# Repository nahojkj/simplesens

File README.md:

# simplesens
simplesne is a simple Arduino-based environment sensing project.

MIT Licensed

The project consists of: 
  1. KiCAD schematic and layout
  2. GERBER production files for PCB
  3. Arduino code and binaries

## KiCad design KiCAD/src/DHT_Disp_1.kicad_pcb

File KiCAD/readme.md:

These are the design files for KiCAD

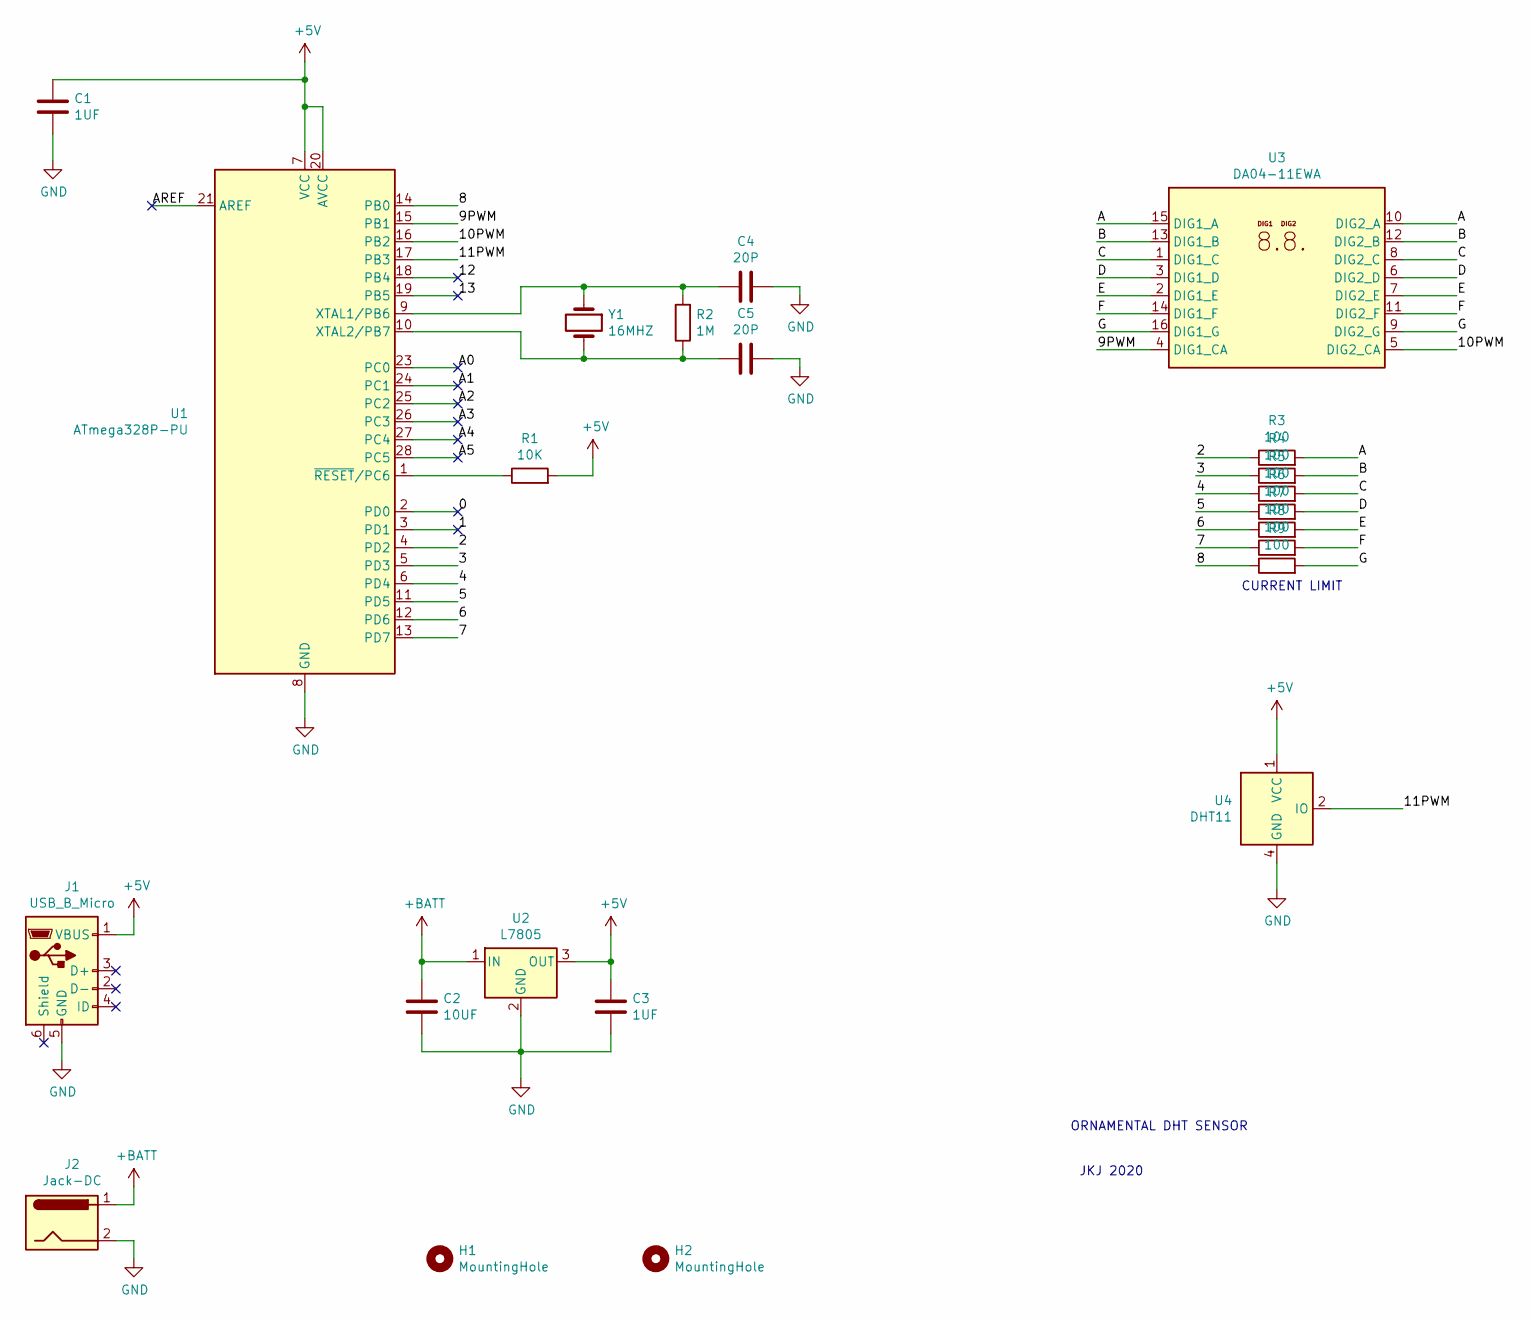
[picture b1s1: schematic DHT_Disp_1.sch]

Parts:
C1, C3: 1UF; C_Radial_D5.0mm_H11.0mm_P2.00mm
C2: 10UF; C_Radial_D5.0mm_H11.0mm_P2.00mm
C4, C5: 20P; C_Disc_D3.0mm_W1.6mm_P2.50mm
H1, H2: MountingHole; MountingHole_3.2mm_M3
J1: USB_B_Micro; USB_Micro-B_GCT_USB3076-30-A
J2: Jack-DC; BarrelJack_Horizontal
R1: 10K; R_Axial_DIN0207_L6.3mm_D2.5mm_P7.62mm_Horizontal
R2: 1M; R_Axial_DIN0207_L6.3mm_D2.5mm_P7.62mm_Horizontal
R3, R4, R5, R6, R7, R8, R9: 100; R_Axial_DIN0207_L6.3mm_D2.5mm_P7.62mm_Horizontal
U1: ATmega328P-PU; DIP-28_W7.62mm
U2: L7805; TO-220-3_Horizontal_TabDown
U3: DA04-11EWA; DA04-11SURKWA
U4: DHT11; Aosong_DHT11_5.5x12.0_P2.54mm
Y1: 16MHZ; Crystal_HC49-U_Vertical

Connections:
+5V: C1.2, C3.1, J1.1 (VBUS), R1.2, U1.7 (VCC), U1.20 (AVCC), U2.3 (OUT), U4.1 (VCC)
+BATT: C2.1, J2.1, U2.1 (IN)
/0: U1.2 (PD0)
/1: U1.3 (PD1)
/2: R3.1, U1.4 (PD2)
/3: R4.1, U1.5 (PD3)
/4: R5.1, U1.6 (PD4)
/5: R6.1, U1.11 (PD5)
/6: R7.1, U1.12 (PD6)
/7: R8.1, U1.13 (PD7)
/8: R9.1, U1.14 (PB0)
/9PWM: U1.15 (PB1), U3.4 (DIG1_CA)
/10PWM: U1.16 (PB2), U3.5 (DIG2_CA)
/11PWM: U1.17 (PB3), U4.2 (IO)
/12: U1.18 (PB4)
/13: U1.19 (PB5)
/A: R3.2, U3.10 (DIG2_A), U3.15 (DIG1_A)
/A0: U1.23 (PC0)
/A1: U1.24 (PC1)
/A2: U1.25 (PC2)
/A3: U1.26 (PC3)
/A4: U1.27 (PC4)
/A5: U1.28 (PC5)
/AREF: U1.21 (AREF)
/B: R4.2, U3.12 (DIG2_B), U3.13 (DIG1_B)
/C: R5.2, U3.1 (DIG1_C), U3.8 (DIG2_C)
/D: R6.2, U3.3 (DIG1_D), U3.6 (DIG2_D)
/E: R7.2, U3.2 (DIG1_E), U3.7 (DIG2_E)
/F: R8.2, U3.11 (DIG2_F), U3.14 (DIG1_F)
/G: R9.2, U3.9 (DIG2_G), U3.16 (DIG1_G)
GND: C1.1, C2.2, C3.2, C4.1, C5.1, J1.5 (GND), J2.2, U1.8 (GND), U1.22 (GND), U2.2 (GND), U4.4 (GND)
unnamed: C4.2, R2.2, U1.9 (XTAL1/PB6), Y1.1
unnamed: C5.2, R2.1, U1.10 (XTAL2/PB7), Y1.2
unnamed: R1.1, U1.1 (~RESET~/PC6)

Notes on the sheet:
CURRENT LIMIT
ORNAMENTAL DHT SENSOR
JKJ 2020

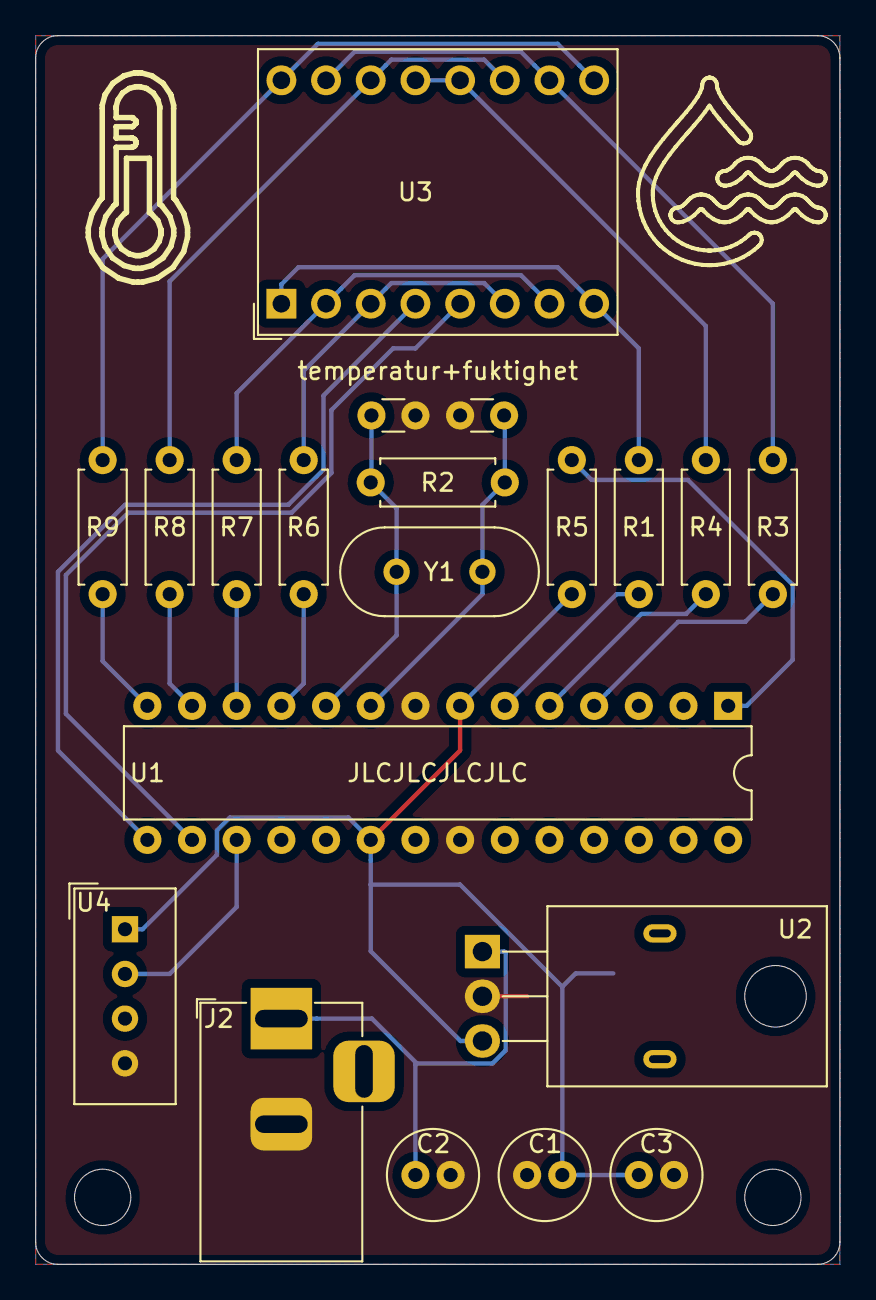
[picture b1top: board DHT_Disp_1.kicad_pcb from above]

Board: 2 copper layers, 45.7 x 69.9 mm, 23 parts (1 on the bottom side), 23 nets.

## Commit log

2020-06-18 Modified readme.md
2020-06-18 Added pdf.-files, removed unwanted files
2020-06-18 Commented source code a little
2021-10-05 Added IntelliSense Configuration
